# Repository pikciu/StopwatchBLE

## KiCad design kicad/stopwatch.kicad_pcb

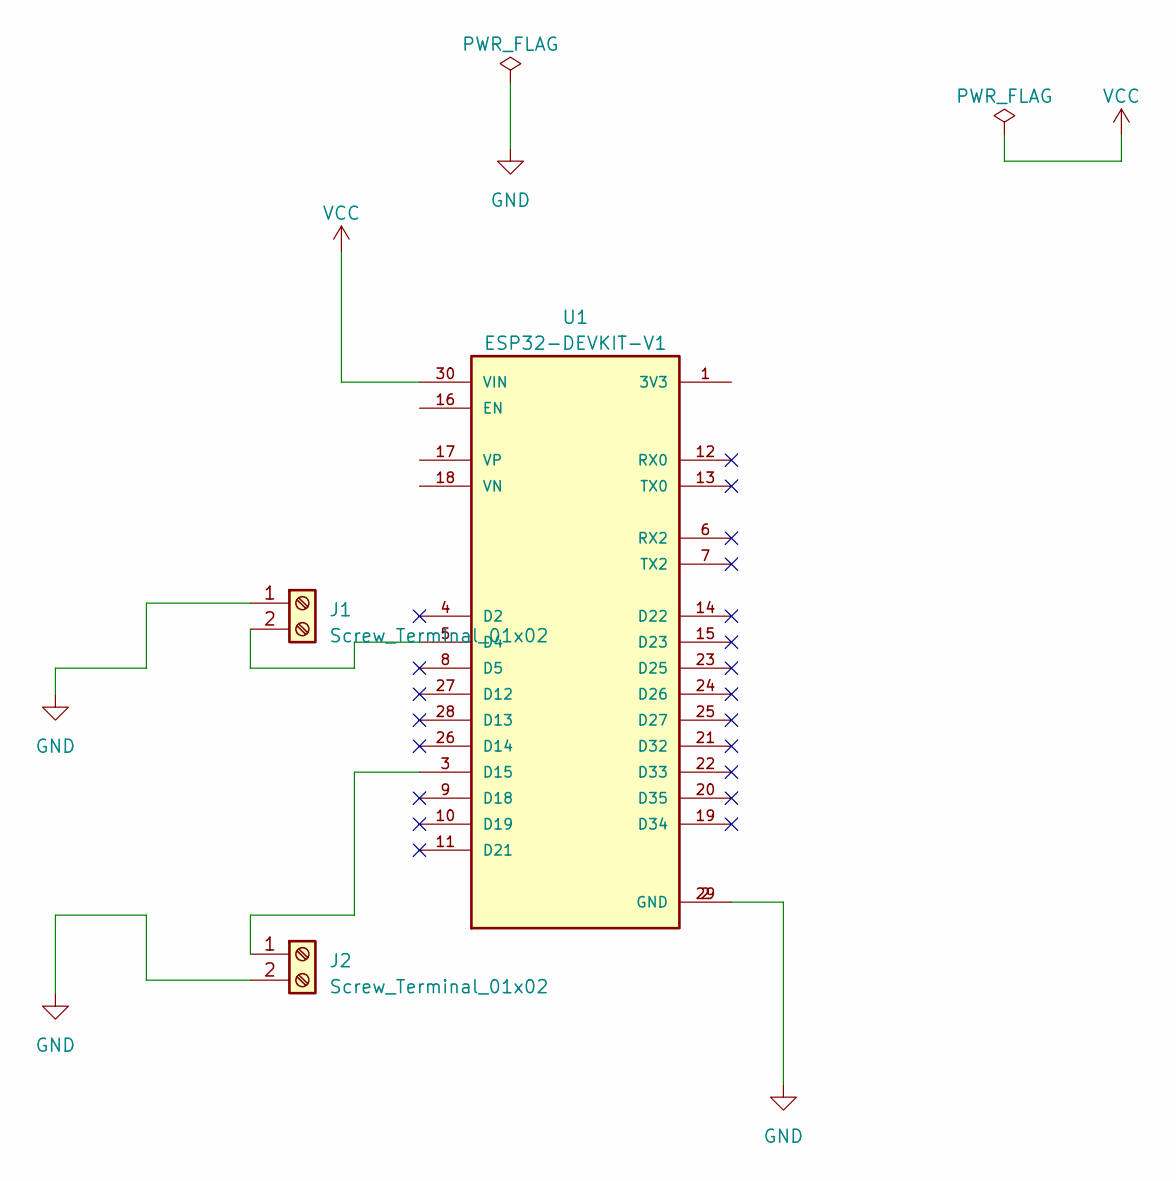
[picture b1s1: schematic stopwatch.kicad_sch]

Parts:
J1, J2: Screw_Terminal_01x02; PhoenixContact_MCV_1,5_2-G-5.08_1x02_P5.08mm_Vertical
U1: ESP32-DEVKIT-V1; MODULE_ESP32_DEVKIT_V1

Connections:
GND: J1.1, J2.2, U1.2 (GND), U1.29 (GND)
unnamed: J1.2, U1.5 (D4)
unnamed: J2.1, U1.3 (D15)
VCC: U1.30 (VIN)

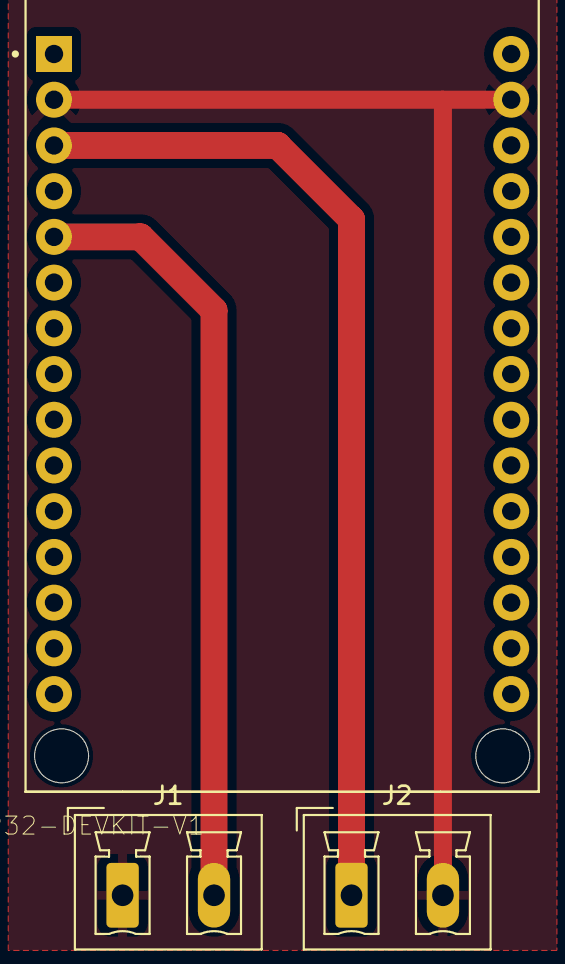
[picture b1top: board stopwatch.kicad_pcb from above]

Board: 2 copper layers, 3 parts (0 on the bottom side), 3 nets.

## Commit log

2023-03-12 stopwatch ble esp32 + iOS
2023-03-13 connect inputs to GND
2023-03-21 android app: timer ui
2023-03-21 android app: bluetooth permissions
2023-03-21 android app: ble connection
2023-03-21 android app: update dependencies
2023-03-23 pcb project
2023-03-30 android: fix bluetooth permissions
2023-04-11 add location permissions
2023-06-25 fix bluetooth permissions
